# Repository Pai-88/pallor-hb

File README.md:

<p align="center">
  Each stripe is one distinct photograph in the dataset, filled with its measured conjunctiva
  colour and ordered by laboratory haemoglobin. Regenerate it with
  <code>python3 scripts/make_banner.py</code>. It is built from derived colour statistics only; no
  dataset photograph is redistributed here.
</p>

---

# PallorHb — Non-Invasive Point-of-Care Anemia Screening

**Estimating blood hemoglobin (Hb) without a needle** from a smartphone image of the palpebral
conjunctiva — and flagging anemia against WHO thresholds. An end-to-end ML study: image → colour
features → regression model → screening decision, with uncertainty reported throughout.

> **Status:** the conjunctiva imaging modality runs on **real public data** (CP-AnemiC, 710
> images with paired lab Hb). A synthetic-PPG demo pipeline is retained for the unit tests.

---

## Headline result

On the public **CP-AnemiC** dataset (Ghanaian children 6–59 months, paired laboratory Hb), twelve
interpretable colour features detect WHO anaemia (Hb < 11 g/dL) with:

**AUROC 0.706 (95 % CI 0.653–0.757)** — fully deduplicated images (three passes, n=383), cross-validated grouped by hospital.

Three findings matter more than that number:

1. **CP-AnemiC has duplicate leakage large enough to change conclusions.** 710 metadata rows
   resolve to only **383 distinct photographs** across three duplicate forms — byte-identical
   files, re-encoded copies, and shifted/re-cropped copies of one photograph saved under different
   IDs (often attributed to different hospitals). 116 final-grain groups carry *conflicting* Hb on
   the same photograph (one spans 3.3–10.4 g/dL), and 125 groups span more than one site — which
   defeats even site-grouped CV. The naive random split inflates AUROC by
   **+0.176** (95 % CI +0.120 to +0.232, p < 0.001).
2. **The image carries the signal.** Demographics alone score 0.524; the image adds
   **+0.182 AUROC** (DeLong p = 2 × 10⁻⁶).
3. **It is a triage screen, not a haemoglobin meter.** Bland–Altman limits of agreement span
   **7.8 g/dL** — ranking works, absolute Hb does not.

Controls designed to make the result fail: label permutation **0.529 ± 0.032** (chance);
10-seed stability **0.702 ± 0.006**; nested-CV hyperparameter tuning does not help (−0.044,
which confirms the fixed settings were not selected for flattery). Sensitivity: the result is flat across
thumbnail thresholds 0.5–5.0, and varies 0.685–0.728 across alignment thresholds 1.0–4.0 (reported,
not hidden).

**→ Full method, tables, controls, figures and limitations: [FINDINGS.md](FINDINGS.md)**

```bash
pip install -r requirements.txt
# unpack CP-AnemiC into data/cp-anemic/ — see FINDINGS.md
python3 scripts/run_full_analysis.py     # ~9 min first run (alignment pass cached after), writes results/
python3 -m pytest tests/ -q              # 62 tests incl. adversarial leakage guards
```

---

## Background

Anemia affects roughly **2 billion people** and is a leading cause of morbidity in pregnancy and
childhood, disproportionately in low-resource settings. The gold standard (a venous draw + lab CBC,
or a HemoCue cuvette) needs consumables, a phlebotomist, and cold-chain logistics. A **non-invasive,
reagent-free, sub-$20 screener** that runs on a microcontroller would let community health workers
triage who actually needs a confirmatory lab test.

This is *screening*, not diagnosis. The design target is high **sensitivity** at the WHO anemia cutoff
(so few true anemics are missed), with the model's uncertainty surfaced rather than hidden.

## The clinical target

| Population        | Anemia threshold (Hb) |
|-------------------|-----------------------|
| Children 6–59 mo  | < 11.0 g/dL           |
| Non-preg. women   | < 12.0 g/dL           |
| Pregnant women    | < 11.0 g/dL           |
| Men               | < 13.0 g/dL           |

Success is measured against a **reference Hb** (lab CBC or HemoCue) using:
- **MAE / RMSE** in g/dL and **Bland–Altman** limits of agreement (the right tool for method
  comparison — a high R² can still hide a clinically unacceptable bias).
- **Sensitivity / specificity** at the population-appropriate cutoff, with the operating point chosen
  to prioritise sensitivity.

## Approach

Two complementary, cheap modalities:

1. **Conjunctiva pallor (this study).** An image of the lower-eyelid conjunctiva; pallor
   (reduced redness) correlates with low Hb. Handled as a colour-feature regression over the
   annotated region of interest.
2. **PPG (possible future modality).** A reflectance sensor on a fingertip; waveform morphology
   carries Hb-related signal. Only a synthetic demo pipeline exists here
   (`python -m pallor_hb.train`), kept because the unit tests exercise it.

Pipeline: `capture → preprocess/QC → feature extraction → regression (calibrated) → Hb estimate + anemia flag + uncertainty`.

## What runs today

```bash
python -m venv .venv && source .venv/bin/activate
pip install -r requirements.txt

# Train + evaluate on synthetic PPG-feature data (writes plots + metrics to results/)
python -m pallor_hb.train --modality ppg --n 2000 --seed 0
```

This generates a physiologically-motivated synthetic dataset, fits a gradient-boosted regressor,
and writes `results/metrics.json`, a Bland–Altman plot, and a predicted-vs-actual plot. It is a
**placeholder for real data**; it exists so that the feature extraction, model, and clinical
evaluation stay wired together and unit-tested.

## Repository layout

```
pallor-hb/
├── README.md
├── requirements.txt
├── src/pallor_hb/
│   ├── dataset.py          # loaders + synthetic data generator
│   ├── features.py         # PPG waveform + conjunctiva colour features
│   ├── model.py            # regression model wrapper
│   ├── evaluate.py         # MAE/RMSE, Bland–Altman, sensitivity/specificity
│   ├── train.py            # end-to-end train/eval entry point
│   ├── experiment.py       # split strategies, ablations, controls
│   ├── stats.py            # DeLong test, bootstrap CIs, calibration
│   └── plots.py            # publication figures, one shared house style
├── scripts/
│   ├── run_full_analysis.py  # single entry point for the CP-AnemiC study
│   └── make_banner.py        # README banner, generated from the data
├── data/                   # dataset pointers (no PHI committed)
├── results/                # figures + metric tables (regenerated)
└── tests/                  # 62 tests, organised by failure mode
```

## Data

See [`data/README.md`](data/README.md) for the CP-AnemiC source, unpack location and integrity
caveats. **No patient data is committed to this repo.**

## Limitations

- Skin tone, perfusion, motion, and ambient light are real confounders; the model must be validated
  *across* skin tones or it will fail the people it most needs to serve.
- This is a personal research/portfolio project, **not a medical device** and not for clinical use.
- Full limitations for the CP-AnemiC study are in [FINDINGS.md](FINDINGS.md#limitations).

## Provenance and attribution

**Data.** The CP-AnemiC dataset is third-party and public — Asare, Appiahene & Donkoh (2023),
Mendeley Data [`m53vz6b7fx`](https://data.mendeley.com/datasets/m53vz6b7fx/1) — used under its
published licence and cited in [FINDINGS.md](FINDINGS.md#data-citation). I did not collect it. No
dataset images or patient data are committed to this repository; the loader reads a local copy that
each user downloads themselves.

**What this repository contributes.** The dataset-integrity audit (duplicate detection at byte, pixel and shifted-copy
level, and the finding that 116 final-grain duplicate groups carry conflicting haemoglobin labels), the
leakage quantification, the mask-aware feature extraction, the evaluation design, and the controls.
The reported AUROC is what remains after the duplicate structure and site grouping documented
here are accounted for, which is why it sits below previously published figures on this dataset;
it is not offered as a state-of-the-art result.

**Prior work.** The published CP-AnemiC benchmark and subsequent papers using it are cited in
FINDINGS.md. Where my numbers disagree with theirs, the disagreement is attributed to evaluation
methodology, and the evidence needed to check that attribution is included.

**Verifiability.** `python3 scripts/run_full_analysis.py` regenerates every number and figure
deterministically (about nine minutes on first run; the alignment pass is cached thereafter), and
`pytest tests/` runs 62 checks including adversarial leakage guards. Every claim in this repository
can be reproduced from source, and `scripts/verify_paper_numbers.py` asserts the manuscript's 62
quoted numbers against the analysis output.

**Status.** Independent portfolio research, not affiliated with or endorsed by UCL, and not
peer-reviewed.

## License

MIT — see [LICENSE](LICENSE). The CP-AnemiC dataset is **not** covered by this licence; see its own
terms on Mendeley Data.

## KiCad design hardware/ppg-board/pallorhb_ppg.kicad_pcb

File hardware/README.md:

# Hardware — PPG front end

The primary modality is a reflectance PPG at the fingertip. The design lives in
[`ppg-board/`](ppg-board/):

| File | Contents |
|---|---|
| [`constraints.md`](ppg-board/constraints.md) | The measurement physics and the hard requirements. **Read first.** |
| [`design.md`](ppg-board/design.md) | Architecture, net-by-net schematic, BOM, layout plan, firmware contract |
| [`fab.md`](ppg-board/fab.md) | JLCPCB order parameters and design rules |
| [`sourcing.md`](ppg-board/sourcing.md) | Live LCSC stock/price checks and the decisions they forced |
| [`bringup.md`](ppg-board/bringup.md) | Staged bring-up with numeric pass gates |

## Why this is not a MAX30102 board

The original plan here was "ESP32 + MAX30102 breakout". Two things changed it.

**Sourcing.** Every integrated PPG AFE is unusable: the MAX30102 has 6 units in stock at $11.61,
the MAX86141 is a wafer-level package that cannot be hand-soldered, the AFE4404 has 1 unit. A
discrete front end turned out to be both cheaper and abundantly stocked. Details in `sourcing.md`.

**Physics.** More importantly, a two-wavelength AC/DC ratio *cannot* measure total haemoglobin.
Modified Beer–Lambert gives AC/DC|λ ≈ ε_λ(S)·c_Hb·Δd·DPF_λ, so any ratio of two AC/DC values
divides out c_Hb by construction — that is precisely why the ratio-of-ratios measures oxygen
saturation. Adding an isosbestic wavelength and ratioing it the same way just produces a second
saturation estimator.

This board instead measures **DC attenuation versus source–detector distance** at a fixed
wavelength, which yields μ_eff and is concentration-sensitive rather than concentration-cancelling.
Two photodiodes at 6.5 mm and 11.5 mm read the same LED pulse simultaneously, so LED drift cancels
in the ratio. See `constraints.md` for the derivation and the honest limits.

## Capture plan (roadmap W4–W5)

1. Stream 3 wavelengths × 2 detectors at 100 Hz over USB CDC (`design.md` §6.3).
2. Per-beat feature extraction — **note that `src/pallor_hb/features.py` must be rewritten first**;
   four of the nine feature columns are currently dead on real waveforms (`design.md` §6.5).
3. Quality gating on TIA headroom and dark level, with recorded rejection reasons.

## Safety / scope

Reflectance PPG at the fingertip, battery powered, no mains connection, no electrical stimulation.
LED drive is capped at 30 mA in hardware and 20 mA nominal in firmware, at ≤25% duty.

This is a **research prototype, not a medical device**, and produces a screening index rather than
an absolute haemoglobin value. It is not for clinical use.

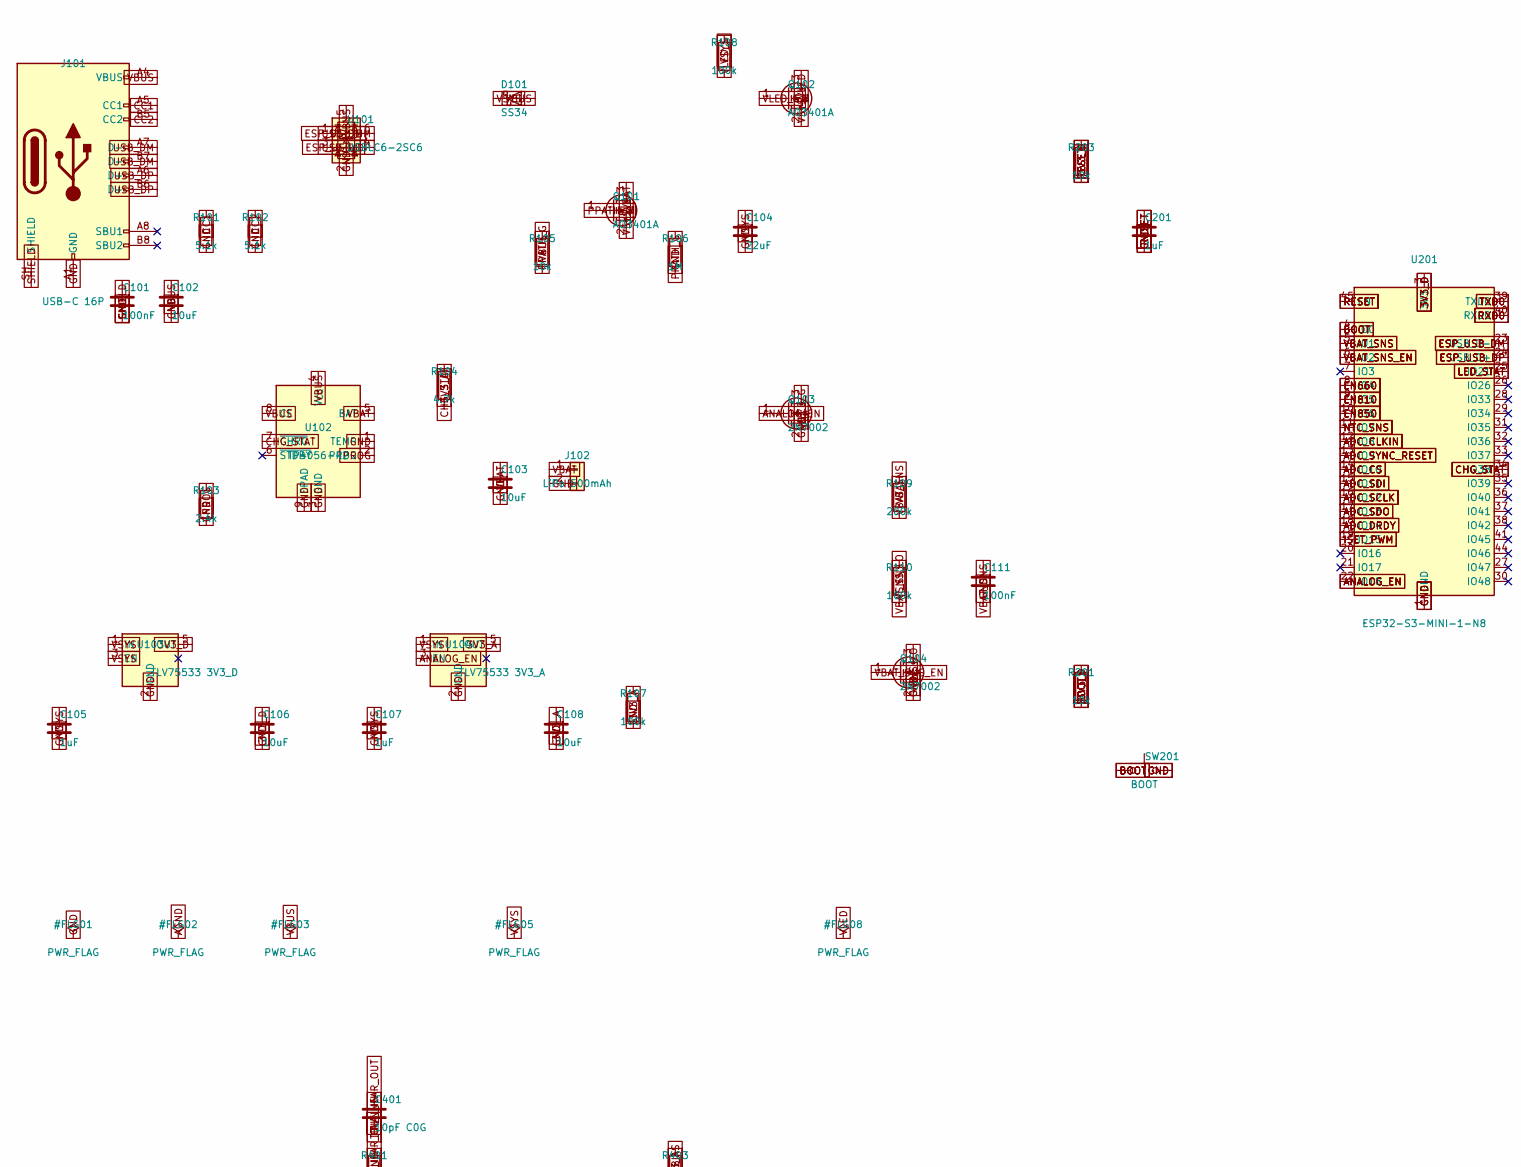
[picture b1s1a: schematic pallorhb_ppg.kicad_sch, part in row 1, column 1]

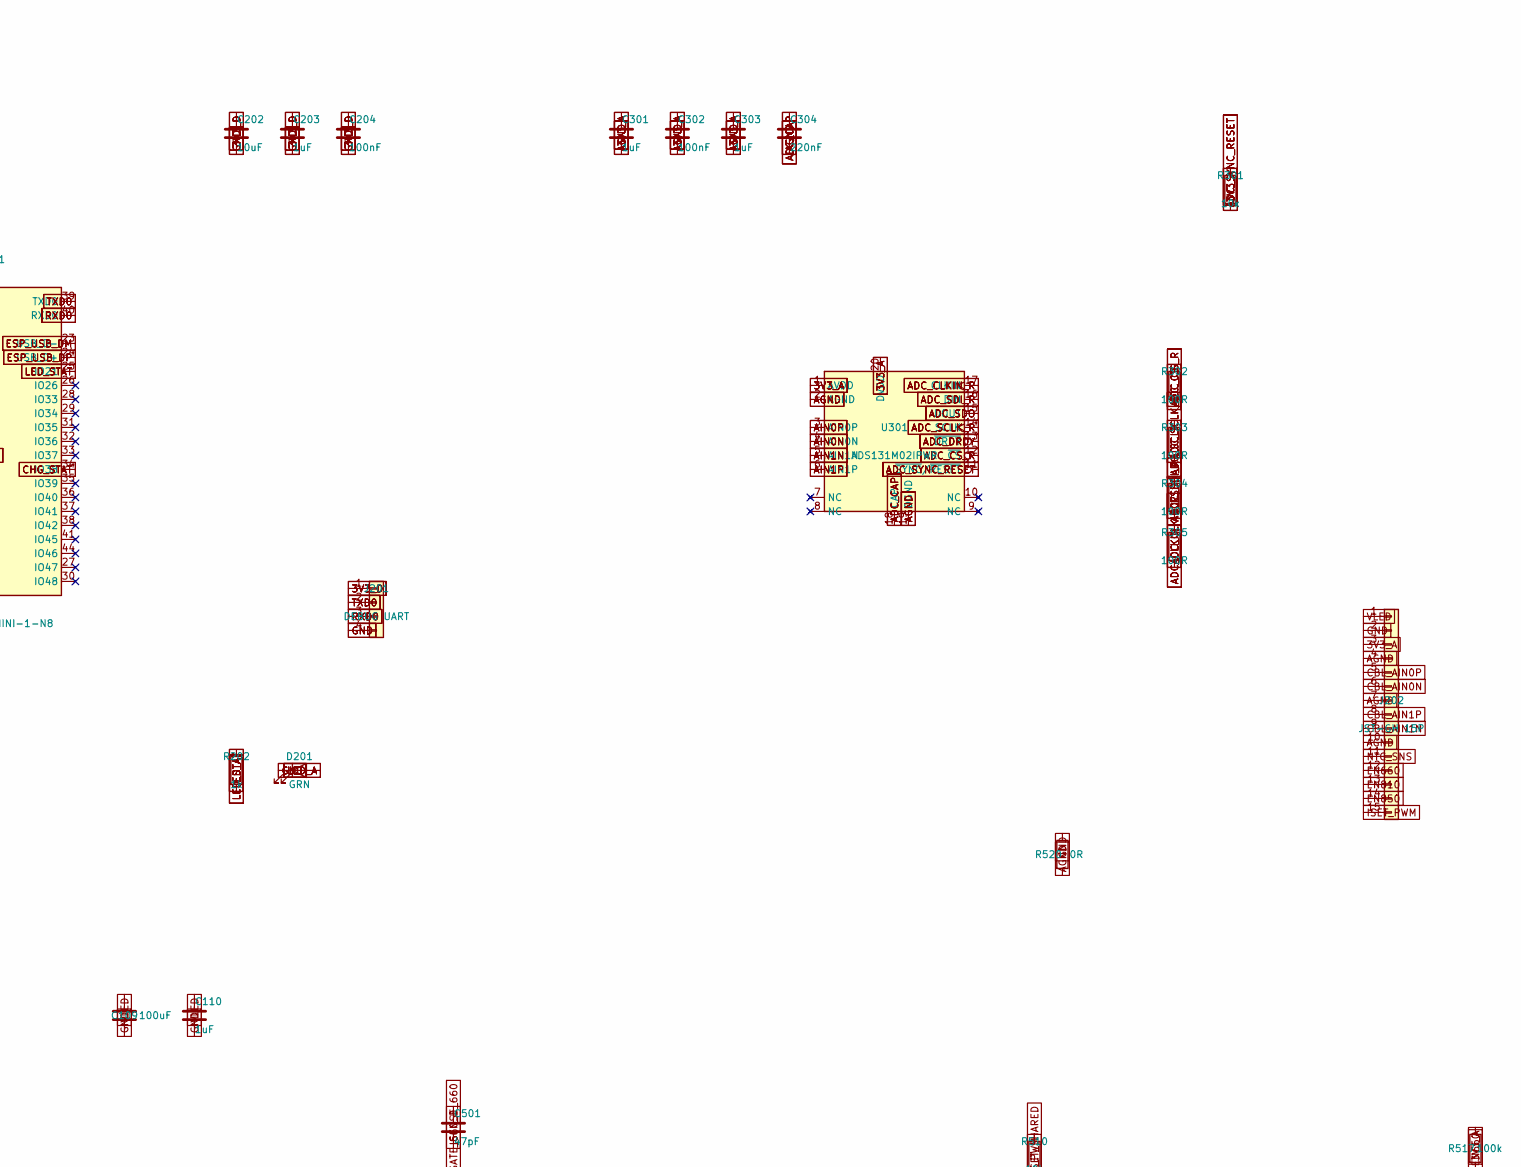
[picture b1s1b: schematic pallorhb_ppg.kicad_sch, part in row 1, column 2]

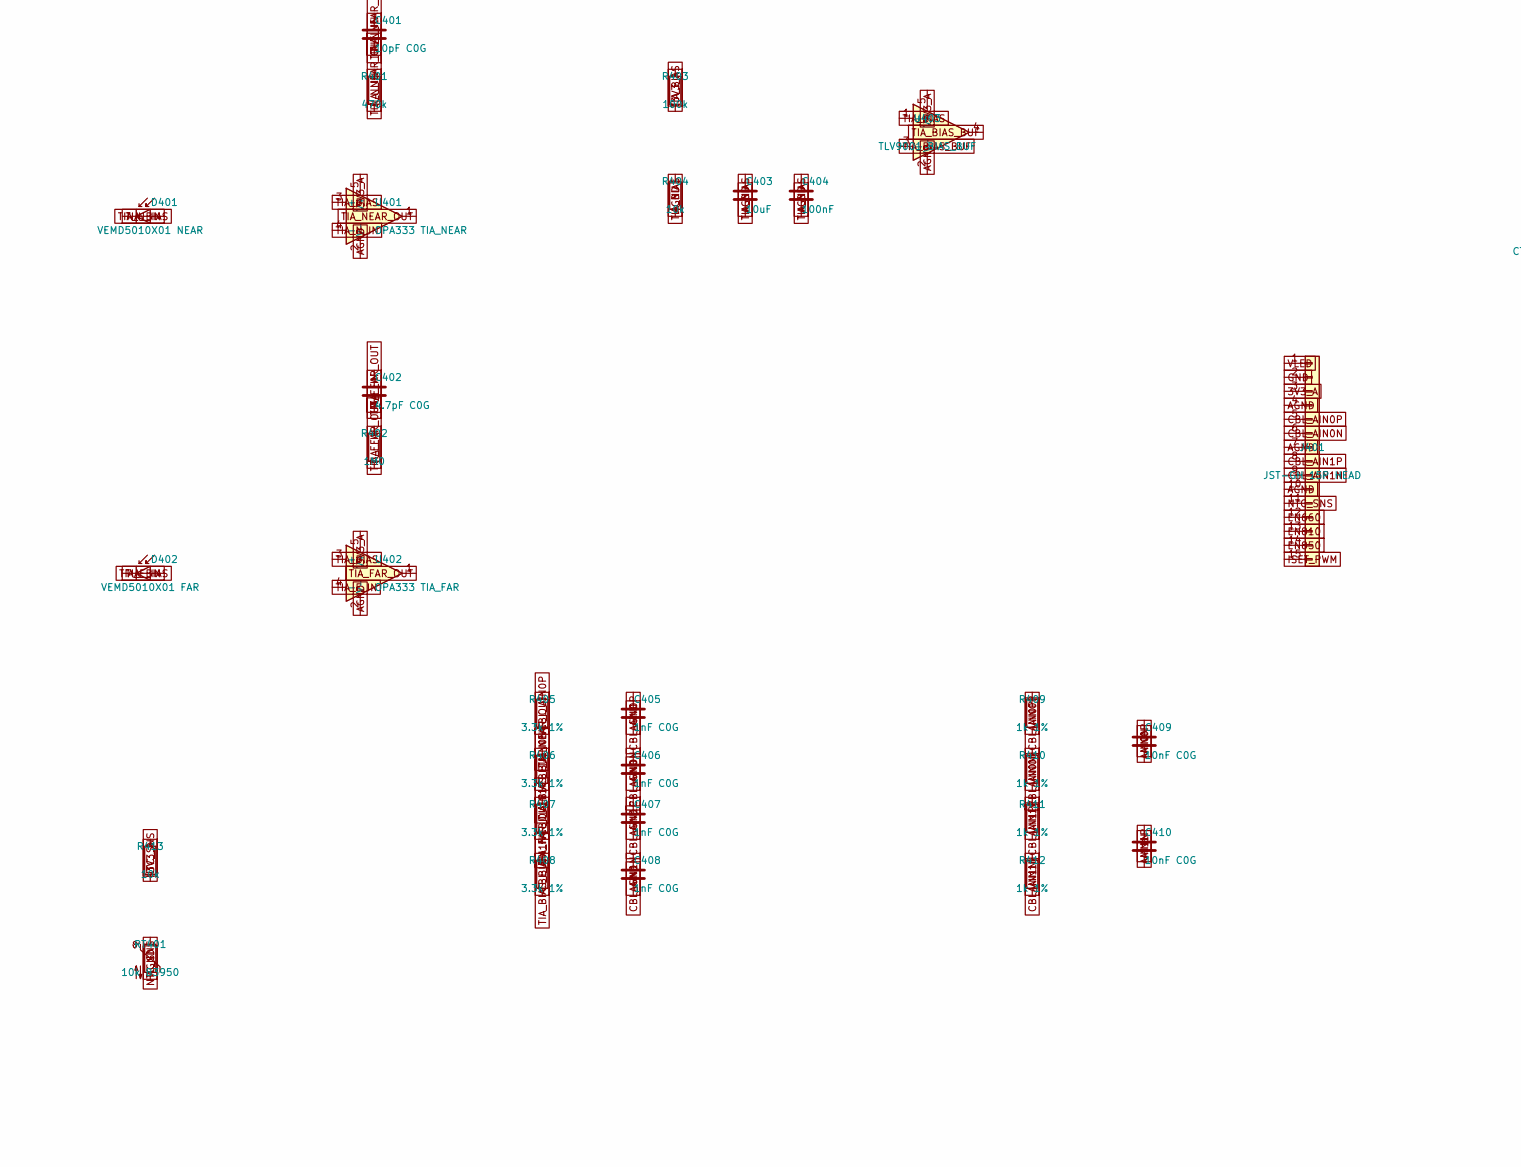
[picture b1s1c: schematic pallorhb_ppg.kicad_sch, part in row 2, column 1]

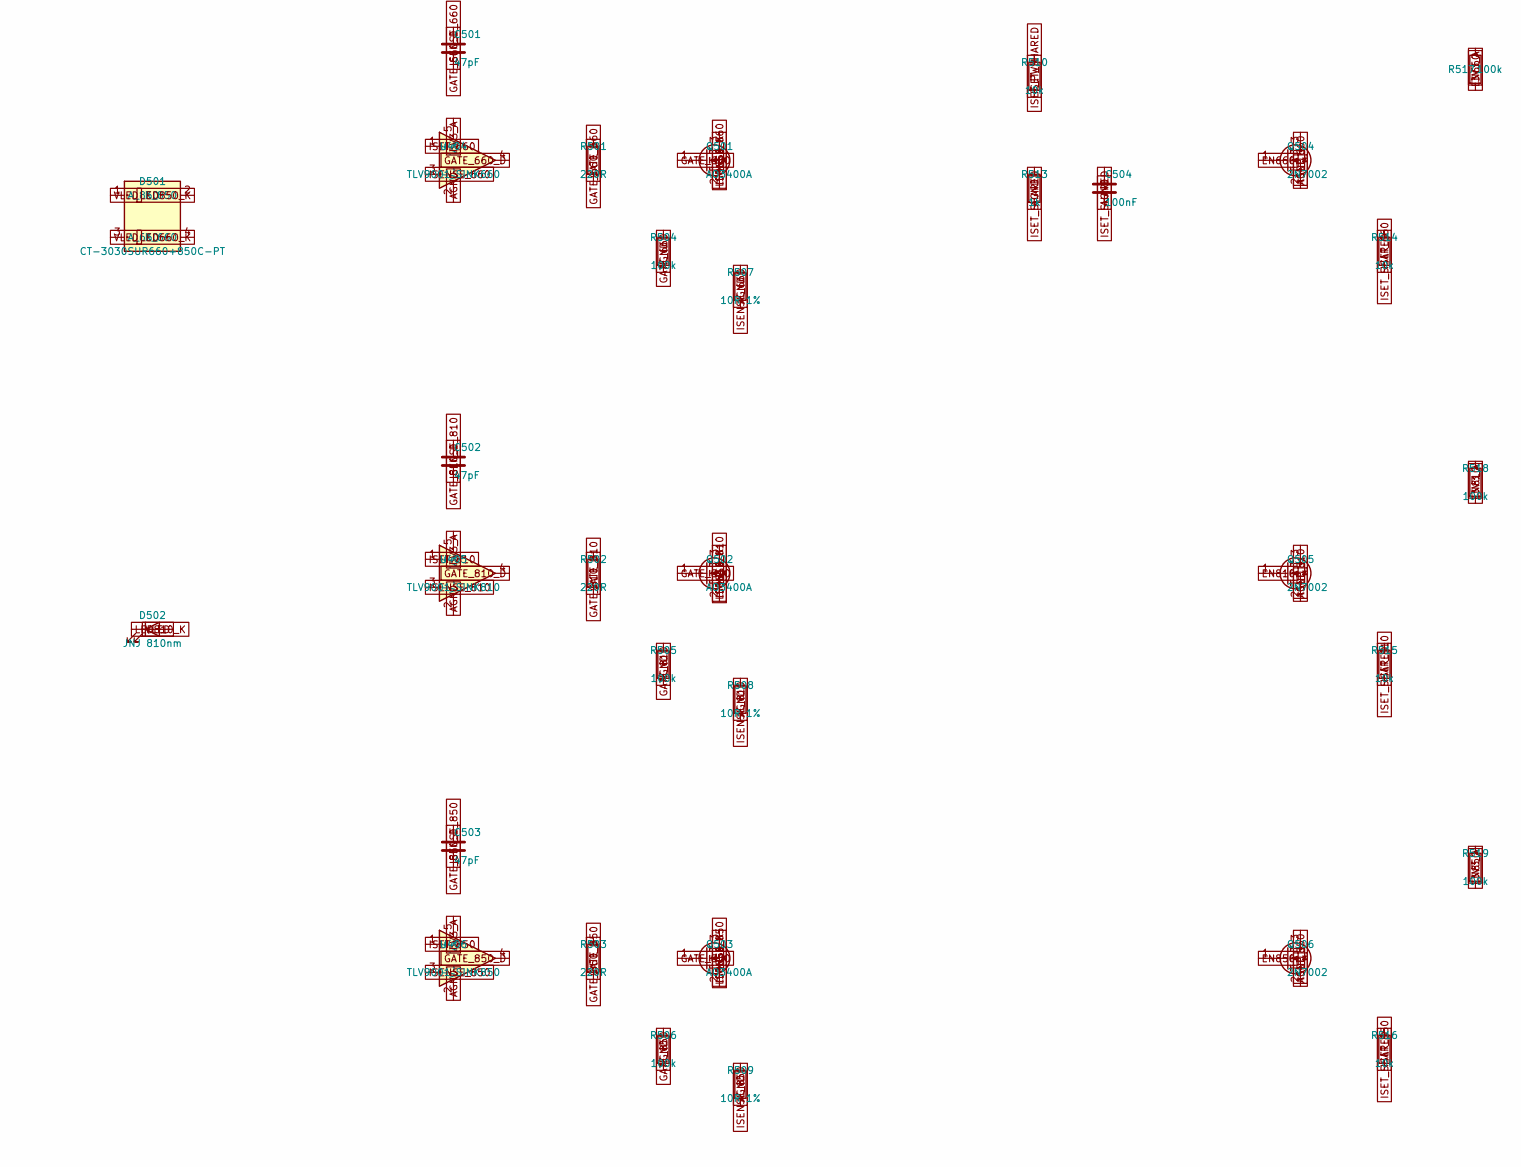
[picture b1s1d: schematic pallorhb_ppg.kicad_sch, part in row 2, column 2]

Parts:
C101, C111, C204, C302, C404, C504: 100nF; C_0402_1005Metric
C102, C103, C106, C108, C202, C403: 10uF; C_0805_2012Metric
C104: 22uF; C_0805_2012Metric
C105, C107, C110, C201, C203, C301, C303: 1uF; C_0603_1608Metric
C109: 100uF; C_1206_3216Metric
C304: 220nF; C_0603_1608Metric
C401: 10pF C0G; C_0402_1005Metric
C402: 4.7pF C0G; C_0402_1005Metric
C405, C406, C407, C408: 1nF C0G; C_0402_1005Metric
C409, C410: 10nF C0G; C_0402_1005Metric
C501, C502, C503: 47pF; C_0402_1005Metric
D101: SS34; D_SMA
D201: GRN; LED_0603_1608Metric
D401: VEMD5010X01 NEAR; VEMD5010X01_PD_5x4mm
D402: VEMD5010X01 FAR; VEMD5010X01_PD_5x4mm
D501: CT-3030SUR660+850C-PT; LED_CT3030_660_850_4P
D502: JNJ 810nm; LED_JNJ3535_IR810_3P
J101: USB-C 16P; USB_C_Receptacle_HRO_TYPE-C-31-M-12
J102: LiPo 500mAh; JST_PH_S2B-PH-SM4-TB_1x02-1MP_P2.00mm_Horizontal
J201: DEBUG UART; PinHeader_1x04_P2.54mm_Vertical
J202: JST-GH 15P; JST_GH_SM15B-GHS-TB_1x15-1MP_P1.25mm_Horizontal
J401: JST-GH 15P HEAD; JST_GH_SM15B-GHS-TB_1x15-1MP_P1.25mm_Horizontal
Q101, Q102: AO3401A; SOT-23
Q103, Q104, Q504, Q505, Q506: 2N7002; SOT-23
Q501, Q502, Q503: AO3400A; SOT-23
R101, R102: 5.1k; R_0603_1608Metric
R103: 2.4k; R_0603_1608Metric
R104: 4.7k; R_0603_1608Metric
R105, R201, R203, R301, R404, R413, R510, R514, R515, R516: 10k; R_0603_1608Metric
R106: 1M; R_0603_1608Metric
R107, R108, R110, R403, R504, R505, R506, R517, R518, R519: 100k; R_0603_1608Metric
R109: 200k; R_0603_1608Metric
R202, R513: 1k; R_0603_1608Metric
R302, R303, R304, R305: 100R; R_0603_1608Metric
R401: 470k; R_0603_1608Metric
R402: 1M0; R_0603_1608Metric
R405, R406, R407, R408: 3.3k 1%; R_0603_1608Metric
R409, R410, R411, R412: 1k 1%; R_0603_1608Metric
R501, R502, R503: 220R; R_0603_1608Metric
R507, R508, R509: 10R 1%; R_0805_2012Metric
R520: 0R; R_0603_1608Metric
RT401: 10k B3950; R_0603_1608Metric
SW201: BOOT; SW_SPST_TL3342
U101: USBLC6-2SC6; SOT-23-6
U102: TP4056-42; ESOP-8_3.9x4.9mm_P1.27mm_EP2.3x3.0mm
U103: TLV75533 3V3_D; SOT-23-5
U104: TLV75533 3V3_A; SOT-23-5
U201: ESP32-S3-MINI-1-N8; ESP32-S2-MINI-1
U301: ADS131M02IPWR; TSSOP-20_4.4x6.5mm_P0.65mm
U401: OPA333 TIA_NEAR; SOT-23-5
U402: OPA333 TIA_FAR; SOT-23-5
U403: TLV9001 BIAS_BUF; SOT-23-5
U404: TLV9001 SINK660; SOT-23-5
U405: TLV9001 SINK810; SOT-23-5
U406: TLV9001 SINK850; SOT-23-5

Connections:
3V3_A: C108.1, C301.1, C302.1, C303.1, J202.3, J401.3, R107.1, R301.1, R403.1, R413.1, R517.1, R518.1, R519.1, U104.5 (OUT), U301.1 (AVDD), U301.20 (DVDD), U401.5 (V+), U402.5 (V+), U403.5 (V+), U404.5 (V+), U405.5 (V+), U406.5 (V+)
3V3_D: C106.1, C202.1, C203.1, C204.1, J201.1, R104.2, R201.1, R203.1, U103.5 (OUT), U201.3 (3V3)
ADC_CAP: C304.1, U301.18 (CAP)
ADC_CLKIN: R305.1, U201.12 (IO8)
ADC_CLKIN_R: R305.2, U301.17 (CLKIN)
ADC_CS: R302.1, U201.14 (IO10)
ADC_CS_R: R302.2, U301.12 (~CS)
ADC_DRDY: U201.18 (IO14), U301.13 (~DRDY)
ADC_SCLK: R303.1, U201.16 (IO12)
ADC_SCLK_R: R303.2, U301.14 (SCLK)
ADC_SDI: R304.1, U201.15 (IO11)
ADC_SDI_R: R304.2, U301.16 (DIN)
ADC_SDO: U201.17 (IO13), U301.15 (DOUT)
ADC_SYNC_RESET: R301.2, U201.13 (IO9), U301.11 (~SYNC/~RESET)
AGND: C301.2, C302.2, C303.2, C304.2, C403.2, C404.2, C405.2, C406.2, C407.2, C408.2, C504.2, J202.4, J202.7, J202.10, J401.4, J401.7, J401.10, Q504.2 (S), Q505.2 (S), Q506.2 (S), R404.2, R504.2, R505.2, R506.2, R507.2, R508.2, R509.2, R513.2, R520.2, RT401.2, U301.2 (AGND), U301.19 (DGND), U401.2 (V-), U402.2 (V-), U403.2 (V-), U404.2 (V-), U405.2 (V-), U406.2 (V-)
AIN0N: C409.2, R410.2, U301.4 (AIN0N)
AIN0P: C409.1, R409.2, U301.3 (AIN0P)
AIN1N: C410.2, R412.2, U301.5 (AIN1N)
AIN1P: C410.1, R411.2, U301.6 (AIN1P)
ANALOG_EN: Q103.1 (G), U104.3 (EN), U201.22 (IO18)
BOOT: R201.2, SW201.1, U201.4 (IO0)
CBL_AIN0N: C406.1, J202.6, J401.6, R406.2, R410.1
CBL_AIN0P: C405.1, J202.5, J401.5, R405.2, R409.1
CBL_AIN1N: C408.1, J202.9, J401.9, R408.2, R412.1
CBL_AIN1P: C407.1, J202.8, J401.8, R407.2, R411.1
CC1: J101.A5 (CC1), R101.1
CC2: J101.B5 (CC2), R102.1
CHG_STAT: R104.1, U102.7 (~CHRG), U201.34 (IO38)
EN660: J202.12, J401.12, Q504.1 (G), R517.2, U201.8 (IO4)
EN810: J202.13, J401.13, Q505.1 (G), R518.2, U201.9 (IO5)
EN850: J202.14, J401.14, Q506.1 (G), R519.2, U201.10 (IO6)
ESP_USB_DM: U101.6 (I/O1), U201.23 (USB_D-)
ESP_USB_DP: U101.4 (I/O2), U201.24 (USB_D+)
GATE_660: Q501.1 (G), R501.2, R504.1
GATE_660_D: C501.1, R501.1, U404.4
GATE_810: Q502.1 (G), R502.2, R505.1
GATE_810_D: C502.1, R502.1, U405.4
GATE_850: Q503.1 (G), R503.2, R506.1
GATE_850_D: C503.1, R503.1, U406.4
GND: C101.2, C102.2, C103.2, C104.2, C105.2, C106.2, C107.2, C108.2, C109.2, C110.2, C111.2, C201.2, C202.2, C203.2, C204.2, D201.1 (K), J101.A1 (GND), J101.A12 (GND), J101.B1 (GND), J101.B12 (GND), J102.2, J201.4, J202.2, J401.2, Q103.2 (S), Q104.2 (S), R101.2, R102.2, R103.2, R106.2, R107.2, R520.1, SW201.2, U101.2 (GND), U102.1 (TEMP), U102.3 (GND), U102.9 (EPAD), U103.2 (GND), U104.2 (GND), U201.1 (GND), U201.2 (GND), U201.42 (GND), U201.43 (GND), U201.46 (GND), U201.47 (GND), U201.48 (GND), U201.49 (GND), U201.50 (GND), U201.51 (GND), U201.52 (GND), U201.53 (GND), U201.54 (GND), U201.55 (GND), U201.56 (GND), U201.57 (GND), U201.58 (GND), U201.59 (GND), U201.60 (GND), U201.61 (GND), U201.62 (GND), U201.63 (GND), U201.64 (GND), U201.65 (GND)
ISENSE_660: C501.2, Q501.2 (S), R507.1, U404.3 (-)
ISENSE_810: C502.2, Q502.2 (S), R508.1, U405.3 (-)
ISENSE_850: C503.2, Q503.2 (S), R509.1, U406.3 (-)
ISET_660: Q504.3 (D), R514.2, U404.1 (+)
ISET_810: Q505.3 (D), R515.2, U405.1 (+)
ISET_850: Q506.3 (D), R516.2, U406.1 (+)
ISET_PWM: J202.15, J401.15, R510.1, U201.19 (IO15)
ISET_SHARED: C504.1, R510.2, R513.1, R514.1, R515.1, R516.1
LED660_K: D501.4 (K_660), Q501.3 (D)
LED810_K: D502.1 (K), Q502.3 (D)
LED850_K: D501.2 (K_850), Q503.3 (D)
LED_A: D201.2 (A), R202.2
LED_STAT: R202.1, U201.25 (IO21)
NTC_SNS: J202.11, J401.11, R413.2, RT401.1, U201.11 (IO7)
PPATH_G: Q101.1 (G), R105.2, R106.1
PROG: R103.1, U102.2 (PROG)
RESET: C201.1, R203.2, U201.45 (EN)
RXD0: J201.3, U201.40 (RXD0)
SHIELD: C101.1, J101.SH (SHIELD)
TIA_BIAS: C403.1, C404.1, D401.1 (K), D402.1 (K), R403.2, R404.1, U401.3 (+), U402.3 (+), U403.1 (+)
TIA_BIAS_BUF: R406.1, R408.1, U403.3 (-), U403.4
TIA_FAR_OUT: C402.2, R402.2, R407.1, U402.1
TIA_F_IN: C402.1, D402.2 (A), R402.1, U402.4 (-)
TIA_NEAR_OUT: C401.2, R401.2, R405.1, U401.1
TIA_N_IN: C401.1, D401.2 (A), R401.1, U401.4 (-)
TXD0: J201.2, U201.39 (TXD0)
USB_DM: J101.A7 (D-), J101.B7 (D-), U101.1 (I/O1)
USB_DP: J101.A6 (D+), J101.B6 (D+), U101.3 (I/O2)
VBAT: C103.1, J102.1, Q101.3 (D), R109.1, U102.5 (BAT)
VBAT_SNS: C111.1, R109.2, R110.1, U201.5 (IO1)
VBAT_SNS_EN: Q104.1 (G), U201.6 (IO2)
VBUS: C102.1, D101.2 (A), J101.A4 (VBUS), J101.A9 (VBUS), J101.B4 (VBUS), J101.B9 (VBUS), R105.1, U101.5 (VBUS), U102.4 (V_{CC}), U102.8 (CE)
VLED: C109.1, C110.1, D501.1 (A_850), D501.3 (A_660), D502.2 (A), J202.1, J401.1, Q102.3 (D)
VLED_G: Q102.1 (G), Q103.3 (D), R108.2
VSNS_LO: Q104.3 (D), R110.2
VSYS: C104.1, C105.1, C107.1, D101.1 (K), Q101.2 (S), Q102.2 (S), R108.1, U103.1 (IN), U103.3 (EN), U104.1 (IN)

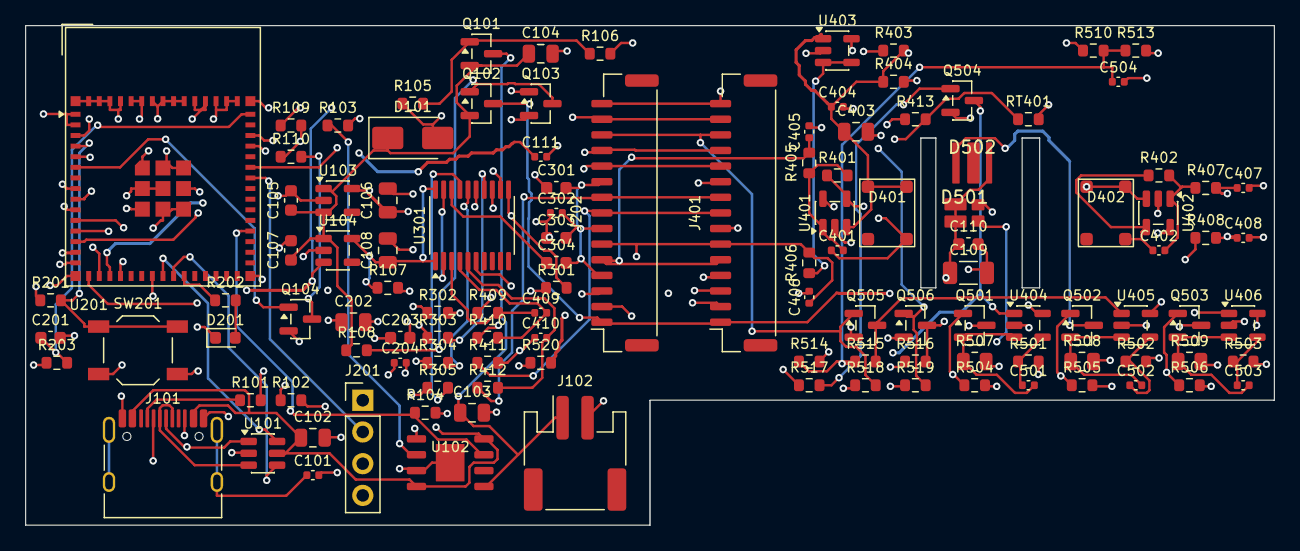
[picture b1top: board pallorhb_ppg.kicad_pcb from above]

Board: 6 copper layers, 100.0 x 40.0 mm, 117 parts (0 on the bottom side), 76 nets.

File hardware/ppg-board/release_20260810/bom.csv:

"Refs","Value","Footprint","Qty"
"C101,C111,C204,C302,C404,C504","100nF","Capacitor_SMD:C_0402_1005Metric","6"
"C102,C103,C106,C108,C202,C403","10uF","Capacitor_SMD:C_0805_2012Metric","6"
"C104","22uF","Capacitor_SMD:C_0805_2012Metric","1"
"C105,C107,C110,C201,C203,C301,C303","1uF","Capacitor_SMD:C_0603_1608Metric","7"
"C109","100uF","Capacitor_SMD:C_1206_3216Metric","1"
"C304","220nF","Capacitor_SMD:C_0603_1608Metric","1"
"C401","10pF C0G","Capacitor_SMD:C_0402_1005Metric","1"
"C402","4.7pF C0G","Capacitor_SMD:C_0402_1005Metric","1"
"C405-C408","1nF C0G","Capacitor_SMD:C_0402_1005Metric","4"
"C409,C410","10nF C0G","Capacitor_SMD:C_0402_1005Metric","2"
"C501-C503","47pF","Capacitor_SMD:C_0402_1005Metric","3"
"D101","SS34","Diode_SMD:D_SMA","1"
"D201","GRN","LED_SMD:LED_0603_1608Metric","1"
"D401","VEMD5010X01 NEAR","pallorhb:VEMD5010X01_PD_5x4mm","1"
"D402","VEMD5010X01 FAR","pallorhb:VEMD5010X01_PD_5x4mm","1"
"D501","CT-3030SUR660+850C-PT","pallorhb:LED_CT3030_660_850_4P","1"
"D502","JNJ 810nm","pallorhb:LED_JNJ3535_IR810_3P","1"
"J101","USB-C 16P","Connector_USB:USB_C_Receptacle_HRO_TYPE-C-31-M-12","1"
"J102","LiPo 500mAh","Connector_JST:JST_PH_S2B-PH-SM4-TB_1x02-1MP_P2.00mm_Horizontal","1"
"J201","DEBUG UART","Connector_PinHeader_2.54mm:PinHeader_1x04_P2.54mm_Vertical","1"
"J202","JST-GH 15P","Connector_JST:JST_GH_SM15B-GHS-TB_1x15-1MP_P1.25mm_Horizontal","1"
"J401","JST-GH 15P HEAD","Connector_JST:JST_GH_SM15B-GHS-TB_1x15-1MP_P1.25mm_Horizontal","1"
"Q101,Q102","AO3401A","Package_TO_SOT_SMD:SOT-23","2"
"Q103,Q104,Q504-Q506","2N7002","Package_TO_SOT_SMD:SOT-23","5"
"Q501-Q503","AO3400A","Package_TO_SOT_SMD:SOT-23","3"
"R101,R102","5.1k","Resistor_SMD:R_0603_1608Metric","2"
"R103","2.4k","Resistor_SMD:R_0603_1608Metric","1"
"R104","4.7k","Resistor_SMD:R_0603_1608Metric","1"
"R105,R201,R203,R301,R404,R413,R510,R514-R516","10k","Resistor_SMD:R_0603_1608Metric","10"
"R106","1M","Resistor_SMD:R_0603_1608Metric","1"
"R107,R108,R110,R403,R504-R506,R517-R519","100k","Resistor_SMD:R_0603_1608Metric","10"
"R109","200k","Resistor_SMD:R_0603_1608Metric","1"
"R202,R513","1k","Resistor_SMD:R_0603_1608Metric","2"
"R302-R305","100R","Resistor_SMD:R_0603_1608Metric","4"
"R401","470k","Resistor_SMD:R_0603_1608Metric","1"
"R402","1M0","Resistor_SMD:R_0603_1608Metric","1"
"R405-R408","3.3k 1%","Resistor_SMD:R_0603_1608Metric","4"
"R409-R412","1k 1%","Resistor_SMD:R_0603_1608Metric","4"
"R501-R503","220R","Resistor_SMD:R_0603_1608Metric","3"
"R507-R509","10R 1%","Resistor_SMD:R_0805_2012Metric","3"
"R520","0R","Resistor_SMD:R_0603_1608Metric","1"
"RT401","10k B3950","Resistor_SMD:R_0603_1608Metric","1"
"SW201","BOOT","Button_Switch_SMD:SW_SPST_TL3342","1"
"U101","USBLC6-2SC6","Package_TO_SOT_SMD:SOT-23-6","1"
"U102","TP4056-42","pallorhb:ESOP-8_3.9x4.9mm_P1.27mm_EP2.3x3.0mm","1"
"U103","TLV75533 3V3_D","Package_TO_SOT_SMD:SOT-23-5","1"
"U104","TLV75533 3V3_A","Package_TO_SOT_SMD:SOT-23-5","1"
"U201","ESP32-S3-MINI-1-N8","RF_Module:ESP32-S2-MINI-1","1"
"U301","ADS131M02IPWR","Package_SO:TSSOP-20_4.4x6.5mm_P0.65mm","1"
"U401","OPA333 TIA_NEAR","Package_TO_SOT_SMD:SOT-23-5","1"
"U402","OPA333 TIA_FAR","Package_TO_SOT_SMD:SOT-23-5","1"
"U403","TLV9001 BIAS_BUF","Package_TO_SOT_SMD:SOT-23-5","1"
"U404","TLV9001 SINK660","Package_TO_SOT_SMD:SOT-23-5","1"
"U405","TLV9001 SINK810","Package_TO_SOT_SMD:SOT-23-5","1"
"U406","TLV9001 SINK850","Package_TO_SOT_SMD:SOT-23-5","1"
